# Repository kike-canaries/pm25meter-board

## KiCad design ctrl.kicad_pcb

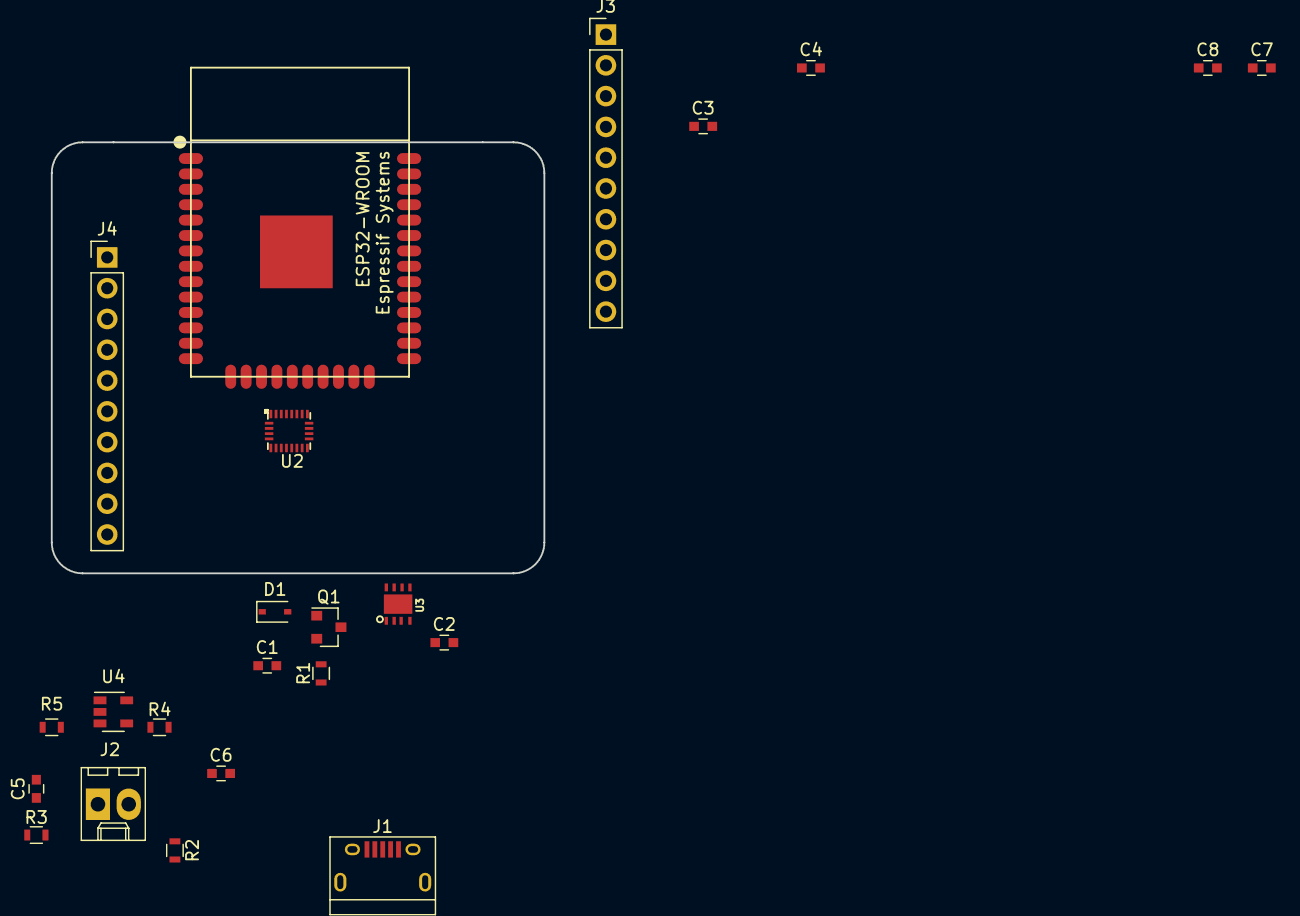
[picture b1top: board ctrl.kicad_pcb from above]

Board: 2 copper layers, 40.6 x 35.6 mm, 23 parts (0 on the bottom side), 10 nets, no tracks yet.

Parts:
C1, C3: 1uF; C_0603
C2: 2.2uF; C_0603
C4: 10uF; C_0603
C5, C6: 4.7uF; C_0603
C7: 10nF; C_0603
C8: 0.1uF; C_0603
D1: BAT20J; D_SOD-323
J1: USB_OTG; USB_Micro-B
J2: LiPo; Molex_KK-6410-02_02x2.54mm_Straight
J3, J4: Conn_01x10; Pin_Header_Straight_1x10_Pitch2.54mm
Q1: DMG2305UX; SOT-23
R1, R3: 2.0k; R_0603
R2: 0; R_0603
R4: DNP; R_0603
R5: 10k; R_0603
U1: ESP32-WROOM
U2: LSM9DS1; LGA-24L
U3: AP7361C-33; 8DFN
U4: MCP73831; SOT-23-5

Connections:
+3V3: C2.1, C3.1, C4.1, R5.1, U1.2, U2.1, U2.3, U2.7, U2.8, U2.22, U2.23, U3.1
+BATT: C5.1, J2.2, Q1.3, U4.3
GND: C1.2, C2.2, C3.2, C4.2, C5.2, C6.2, C7.2, C8.2, J1.5, J1.6, J2.1, R1.2, R3.2, R4.2, U1.1, U1.15, U1.38, U1.39, U2.5, U2.6, U2.14, U2.15, U2.16, U2.17, U2.18, U2.19, U2.20, U3.4, U3.5, U3.PAD, U4.2
unnamed: C1.1, D1.1, Q1.2, U3.8
unnamed: C7.1, U2.21
unnamed: C8.1, U2.24
unnamed: R2.1, R4.1, U4.5
unnamed: R2.2, R3.1
unnamed: R5.2, U2.13
V_USB: C6.1, D1.2, Q1.1, R1.1, U4.4
